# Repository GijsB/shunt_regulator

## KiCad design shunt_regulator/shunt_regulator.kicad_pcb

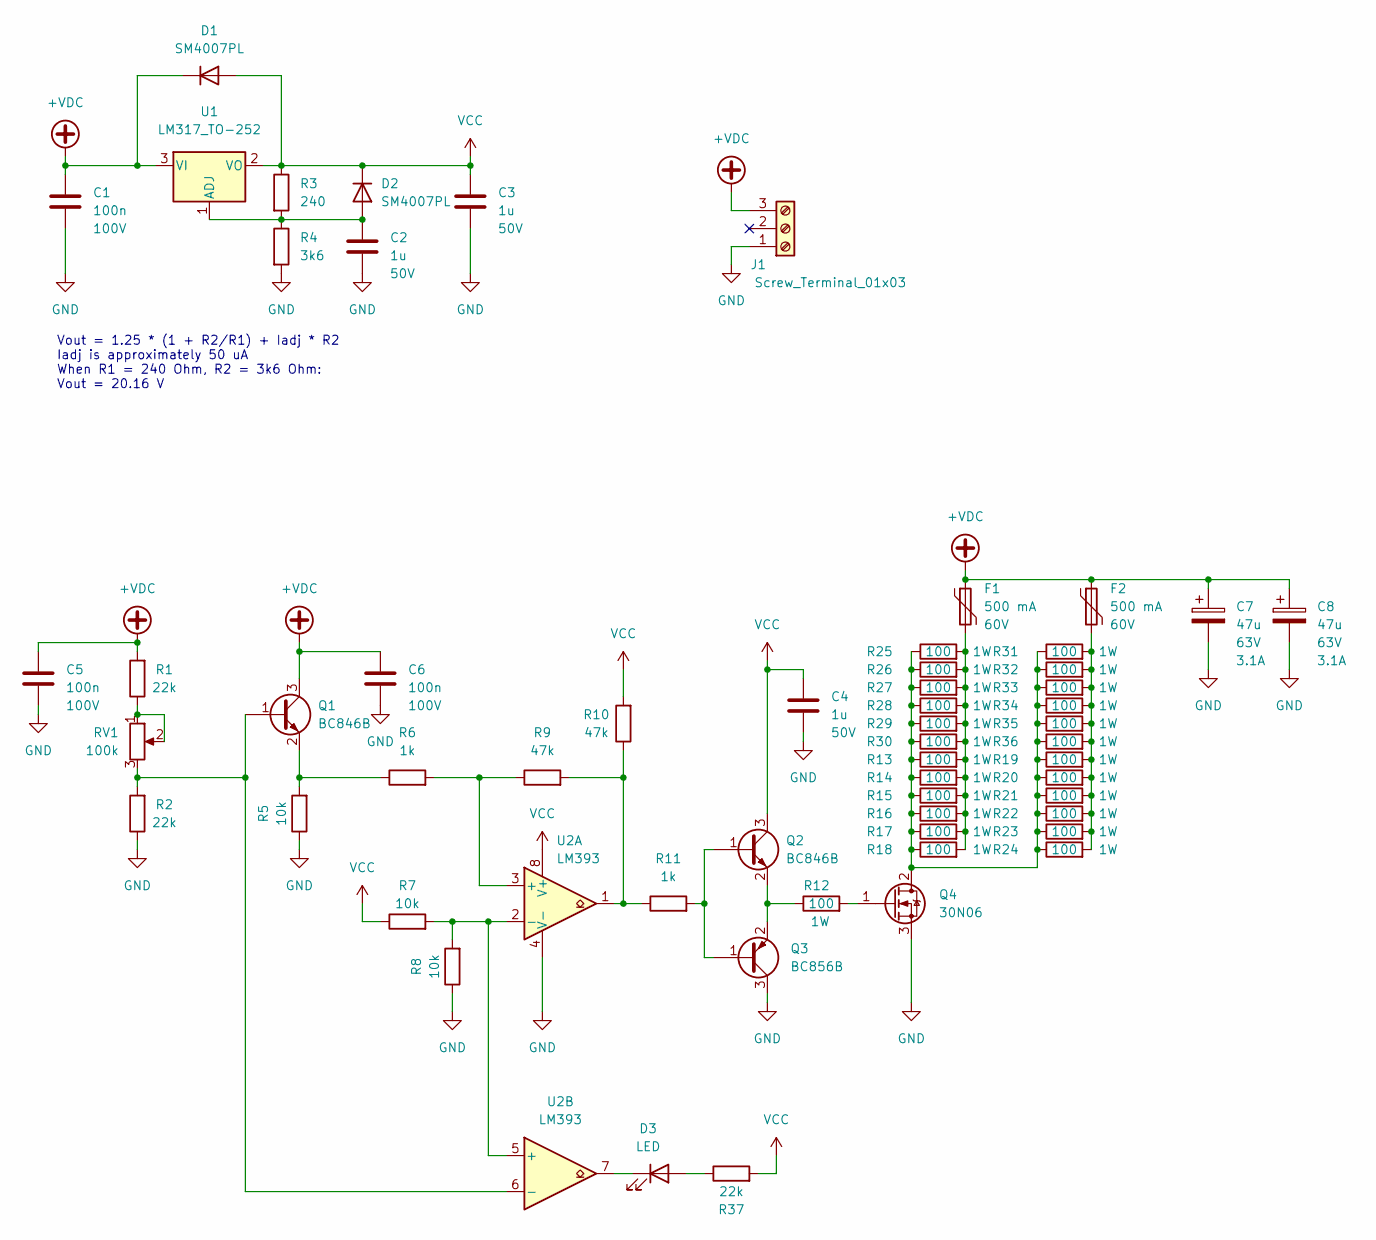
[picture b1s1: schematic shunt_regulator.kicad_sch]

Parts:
C1, C5, C6: 100n; D_0805_2012Metric; Voltage 100V; LCSC C28233
C2, C3, C4: 1u; D_0805_2012Metric; Voltage 50V; LCSC C28323
C7, C8: 47u; CP_Elec_10x10; Voltage 63V; LCSC C178377
D1, D2: SM4007PL; D_SOD-123F; LCSC C64898
D3: LED; LED_0805_2012Metric; LCSC C84256
F1, F2: 500 mA; Fuse_2920_7451Metric; Voltage 60V; LCSC C269176
J1: Screw_Terminal_01x03; Owon SPE terminals
Q1, Q2: BC846B; SOT-23; LCSC C87062
Q3: BC856B; SOT-23; LCSC C424398
Q4: 30N06; TO-252-2; LCSC C369599
R1, R2, R37: 22k; R_0805_2012Metric; LCSC C17560
R3: 240; R_0805_2012Metric; LCSC C17572
R4: 3k6; R_0805_2012Metric; LCSC C18359
R5, R7, R8: 10k; R_0805_2012Metric; LCSC C17724
R6, R11: 1k; R_0805_2012Metric; LCSC C17513
R9, R10: 47k; R_0805_2012Metric; LCSC C17713
R12, R13, R14, R15, R16, R17, R18, R19, R20, R21, R22, R23, R24, R25, R26, R27, R28, R29, R30, R31, R32, R33, R34, R35, R36: 100; R_2512_6332Metric; LCSC C31885
RV1: 100k; Potentiometer_Bourns_3296W_Vertical; LCSC C48084
U1: LM317_TO-252; TO-252-2; LCSC C75510
U2: LM393; SOIC-8_3.9x4.9mm_P1.27mm; LCSC C7955

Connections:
+VDC: C1.1, C5.1, C6.1, C7.1, C8.1, D1.1 (K), F1.1, F2.1, J1.3, Q1.3 (C), R1.2, U1.3 (VI)
GND: C1.2, C2.2, C3.2, C4.2, C5.2, C6.2, C7.2, C8.2, J1.1, Q3.3 (C), Q4.3 (S), R2.1, R4.2, R5.1, R8.1, U2.4 (V-)
unnamed: C2.1, D2.2 (A), R3.2, R4.1, U1.1 (ADJ)
unnamed: D3.1 (K), U2.7
unnamed: D3.2 (A), R37.1
unnamed: F1.2, R13.2, R14.2, R15.2, R16.2, R17.2, R18.2, R25.2, R26.2, R27.2, R28.2, R29.2, R30.2
unnamed: F2.2, R19.2, R20.2, R21.2, R22.2, R23.2, R24.2, R31.2, R32.2, R33.2, R34.2, R35.2, R36.2
unnamed: Q1.2 (E), R5.2, R6.1
unnamed: Q2.2 (E), Q3.2 (E), R12.1
unnamed: Q2.1 (B), Q3.1 (B), R11.2
unnamed: Q4.1 (G), R12.2
unnamed: Q4.2 (D), R13.1, R14.1, R15.1, R16.1, R17.1, R18.1, R19.1, R20.1, R21.1, R22.1, R23.1, R24.1, R25.1, R26.1, R27.1, R28.1, R29.1, R30.1, R31.1, R32.1, R33.1, R34.1, R35.1, R36.1
unnamed: R1.1, RV1.1, RV1.2
unnamed: R6.2, R9.1, U2.3 (+)
unnamed: R9.2, R10.1, R11.1, U2.1
unnamed: R7.2, R8.2, U2.2 (-), U2.5 (+)
unnamed: Q1.1 (B), R2.2, RV1.3, U2.6 (-)
VCC: C3.1, C4.1, D1.2 (A), D2.1 (K), Q2.3 (C), R3.1, R7.1, R10.2, R37.2, U1.2 (VO), U2.8 (V+)

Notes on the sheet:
Vout = 1.25 * (1 + R2/R1) + Iadj * R2 Iadj is approximately 50 uA When R1 = 240 Ohm, R2 = 3k6 Ohm: Vout = 20.16 V

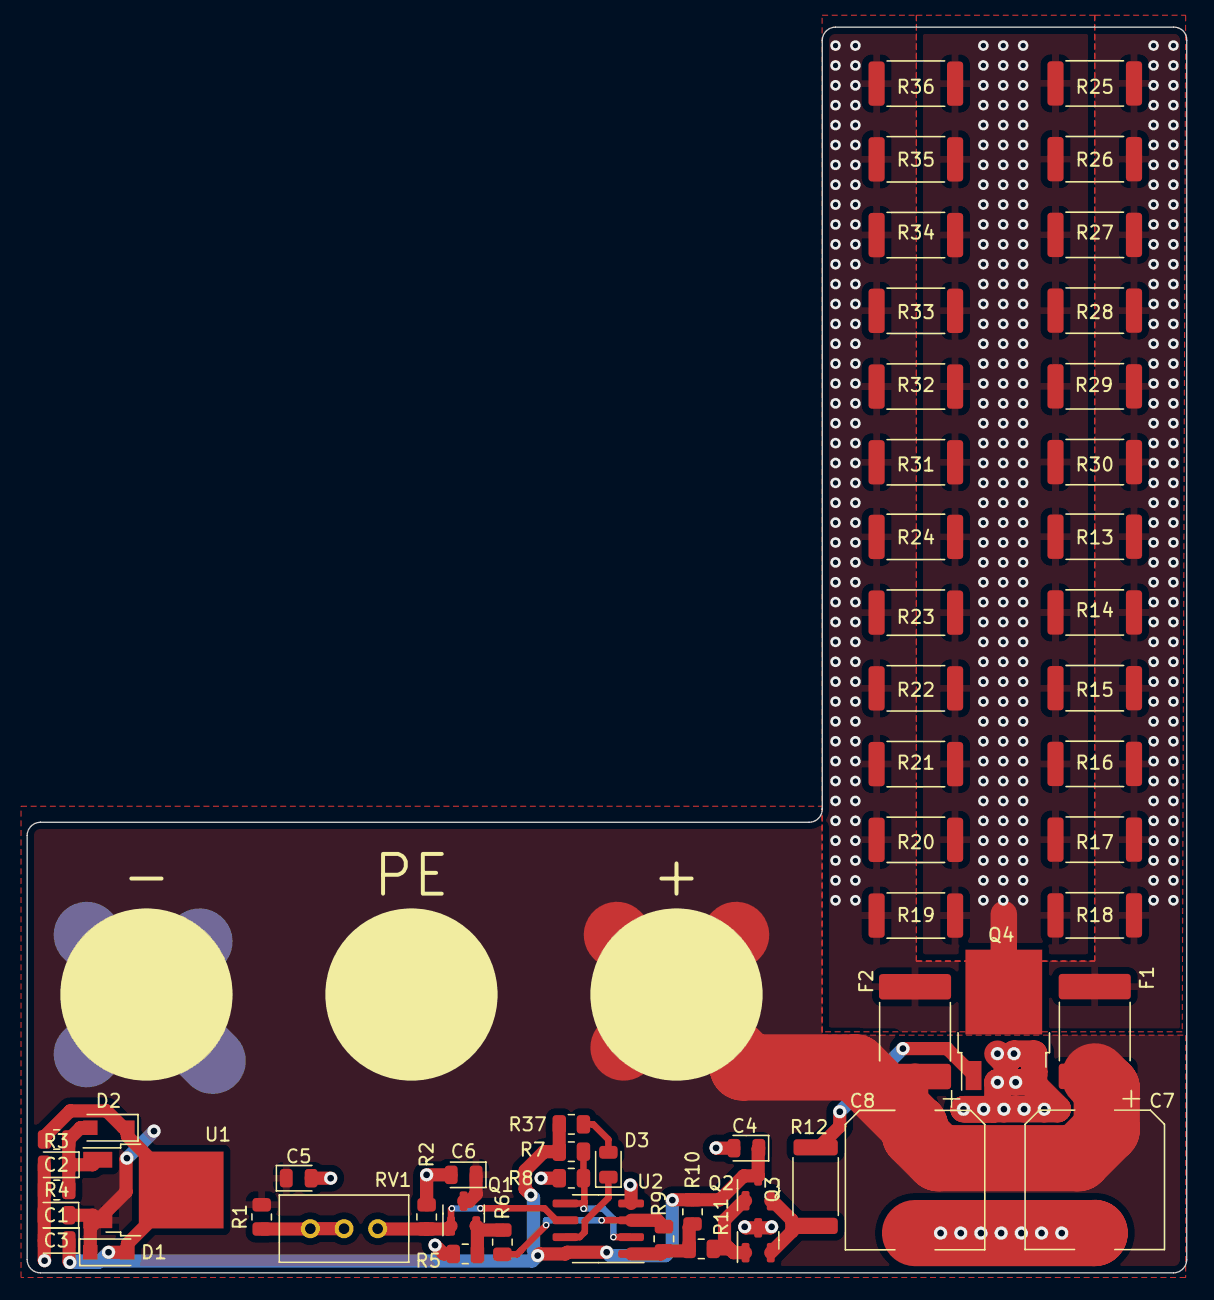
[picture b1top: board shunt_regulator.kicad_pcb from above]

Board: 2 copper layers, 87.5 x 94.0 mm, 58 parts (0 on the bottom side), 18 nets.

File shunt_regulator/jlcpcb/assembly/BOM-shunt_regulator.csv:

Comment,Designator,Footprint,LCSC
1k,"R11,R6",R_0805_2012Metric,C17513
22k,"R1,R2,R37",R_0805_2012Metric,C17560
240,R3,R_0805_2012Metric,C17572
47k,"R10,R9",R_0805_2012Metric,C17713
10k,"R5,R7,R8",R_0805_2012Metric,C17724
47u,"C7,C8",CP_Elec_10x10,C178377
3k6,R4,R_0805_2012Metric,C18359
500 mA,"F1,F2",Fuse_2920_7451Metric,C269176
100n,"C1,C5,C6",D_0805_2012Metric,C28233
1u,"C2,C3,C4",D_0805_2012Metric,C28323
100,"R12,R13,R14,R15,R16,R17,R18,R19,R20,R21,R22,R23,R24,R25,R26,R27,R28,R29,R30,R31,R32,R33,R34,R35,R36",R_1210_3225Metric,C31885
30N06,Q4,TO-252-2,C369599
BC856B,Q3,SOT-23,C424398
100k,RV1,Potentiometer_Bourns_3296W_Vertical,C48084
SM4007PL,"D1,D2",D_SOD-123F,C64898
LM317_TO-252,U1,TO-252-2,C75510
LM393,U2,SOIC-8_3.9x4.9mm_P1.27mm,C7955
LED,D3,LED_0805_2012Metric,C84256
BC846B,"Q1,Q2",SOT-23,C87062

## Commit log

2022-10-16 First kicad schematic and model
2022-10-22 Finished design
2022-10-24 Changed the power resistor footprint from 1210 to 2512
2022-11-02 Fixed the footprint of the power supply, the pins where too close together
2022-11-02 Fixed footprint
2022-11-02 Fixed a push-pull transistor that was the wrong way around
2022-11-02 Flipped input of LED comperator
2022-11-03 Changed the LCSC number of the 10k resistors
2022-11-05 Created more space for dissipation resistors, this way less heat is dunped into the fuses (increasing their rating)
2022-11-05 Removed the backups
2022-11-05 Restructured repo such that the spice model would have it's own folder
2022-11-05 Create LICENSE
2022-11-05 Removed DS_Store from repo
2022-11-05 Written the README up until the experiments
2022-11-05 Forgot to include the REAMDE
2022-11-05 Added a pictore of the 3D model
2022-11-05 Removed temporary spice files
2022-11-06 Updated production outputs and added the one time pulse energy to the README requirements
2022-11-06 Changed the picture of the design in the README, this one is now a bit more descriptive
2022-11-06 Added usage instructions
2022-11-06 Fixed some typos in the README
2022-11-07 Added some experiments showing the performance
